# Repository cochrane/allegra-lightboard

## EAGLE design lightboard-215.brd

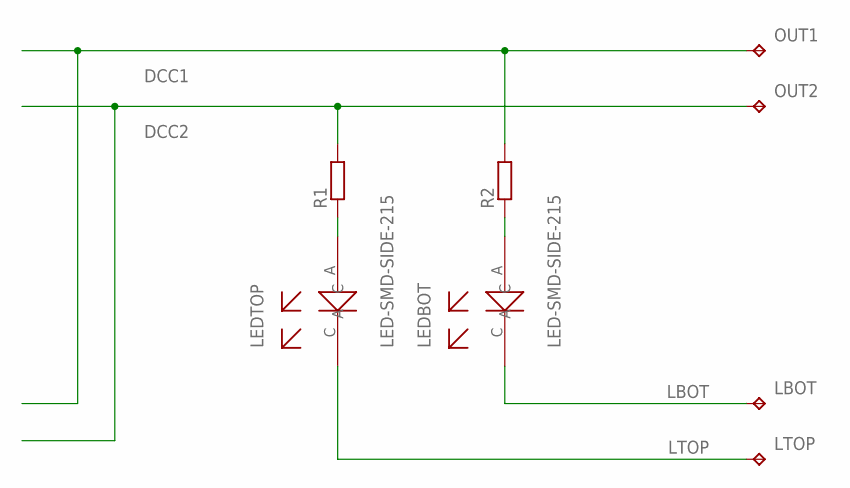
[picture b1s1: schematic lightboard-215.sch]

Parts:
LBOT: TPB1,27; B1,27
LEDBOT: LED-SMD-SIDE-215
LEDTOP: LED-SMD-SIDE-215
LTOP: TPB1,27; B1,27
OUT1, OUT2: TPB1,27; B1,27
R1, R2: R-EU_R0805; R0805

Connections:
DCC1: OUT1.TP, R2.2
DCC2: OUT2.TP, R1.2
LBOT: LBOT.TP, LEDBOT.C
LTOP: LEDTOP.C, LTOP.TP
unnamed: LEDTOP.A, R1.1
unnamed: LEDBOT.A, R2.1

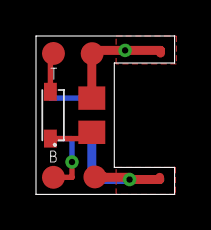
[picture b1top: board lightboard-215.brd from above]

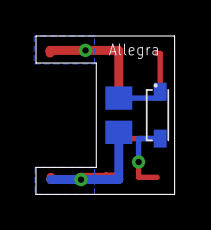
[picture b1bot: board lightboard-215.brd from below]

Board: 2 copper layers, 7.7 x 8.8 mm, 8 parts (2 on the bottom side), 6 nets.

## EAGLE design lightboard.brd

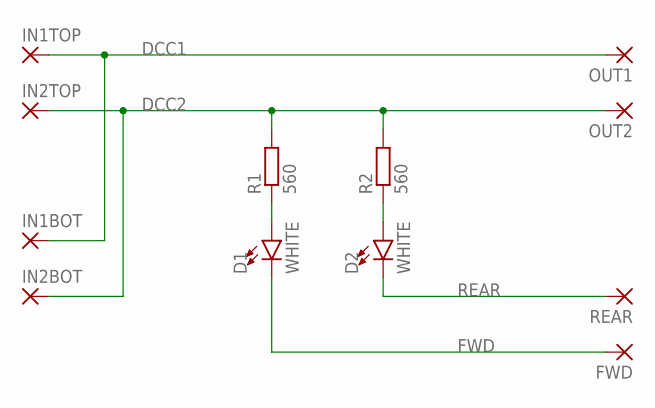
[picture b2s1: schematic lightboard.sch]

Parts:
D1, D2: WHITE; LED-1206
FWD: SMD2; SMD1,27-2,54
IN1BOT, IN1TOP, IN2BOT, IN2TOP: SMD2; SMD1,27-2,54
OUT1, OUT2: SMD2; SMD1,27-2,54
R1, R2: 560; R0603
REAR: SMD2; SMD1,27-2,54

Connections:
DCC1: IN1BOT.1, IN1TOP.1, OUT1.1
DCC2: IN2BOT.1, IN2TOP.1, OUT2.1, R1.2, R2.2
FWD: D1.C, FWD.1
unnamed: D1.A, R1.1
unnamed: D2.A, R2.1
REAR: D2.C, REAR.1

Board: 2 copper layers, 12 parts (4 on the bottom side), 6 nets, no tracks yet.

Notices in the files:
parts and their libraries:
SparkFun-LED: Licensing: Creative Commons ShareAlike 4.0 International - https://creativecommons.org/licenses/by-sa/4.0
